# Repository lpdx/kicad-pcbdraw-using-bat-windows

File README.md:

# Running PcbDraw using bat file
Simple batch script to run [PcbDraw](https://github.com/yaqwsx/PcbDraw) on Windows environment to draw KiCAD pcbs.
The example creates plot for both sides of the pcb.

For more information about PcbDraw please check the [oficial repository](https://github.com/yaqwsx/PcbDraw).

## Dependencies

With KiCAD terminal activated, `kicad-cmd`, install the PcbDraw package using:

```pyhton
pip install pcbdraw
```

## Using it

- Update the [`make-plot-board.bat`](./make-plot-board.bat) file with the appropriate configs (line 11-16)
```cmd
REM config variables
SET ROOT_FILENAME=pwm-interface-board
SET FILE_PATH=./example/
SET CONFIG=--drill-holes --style jlcpcb-green-hasl
REM could be .svg, .png or .jpeg
SET OUTPUT_EXTENSION=.png
```

- Just give a double click on `make-plot-board.bat` or run it from terminal.

_Tested with KiCAD v6.0.10._

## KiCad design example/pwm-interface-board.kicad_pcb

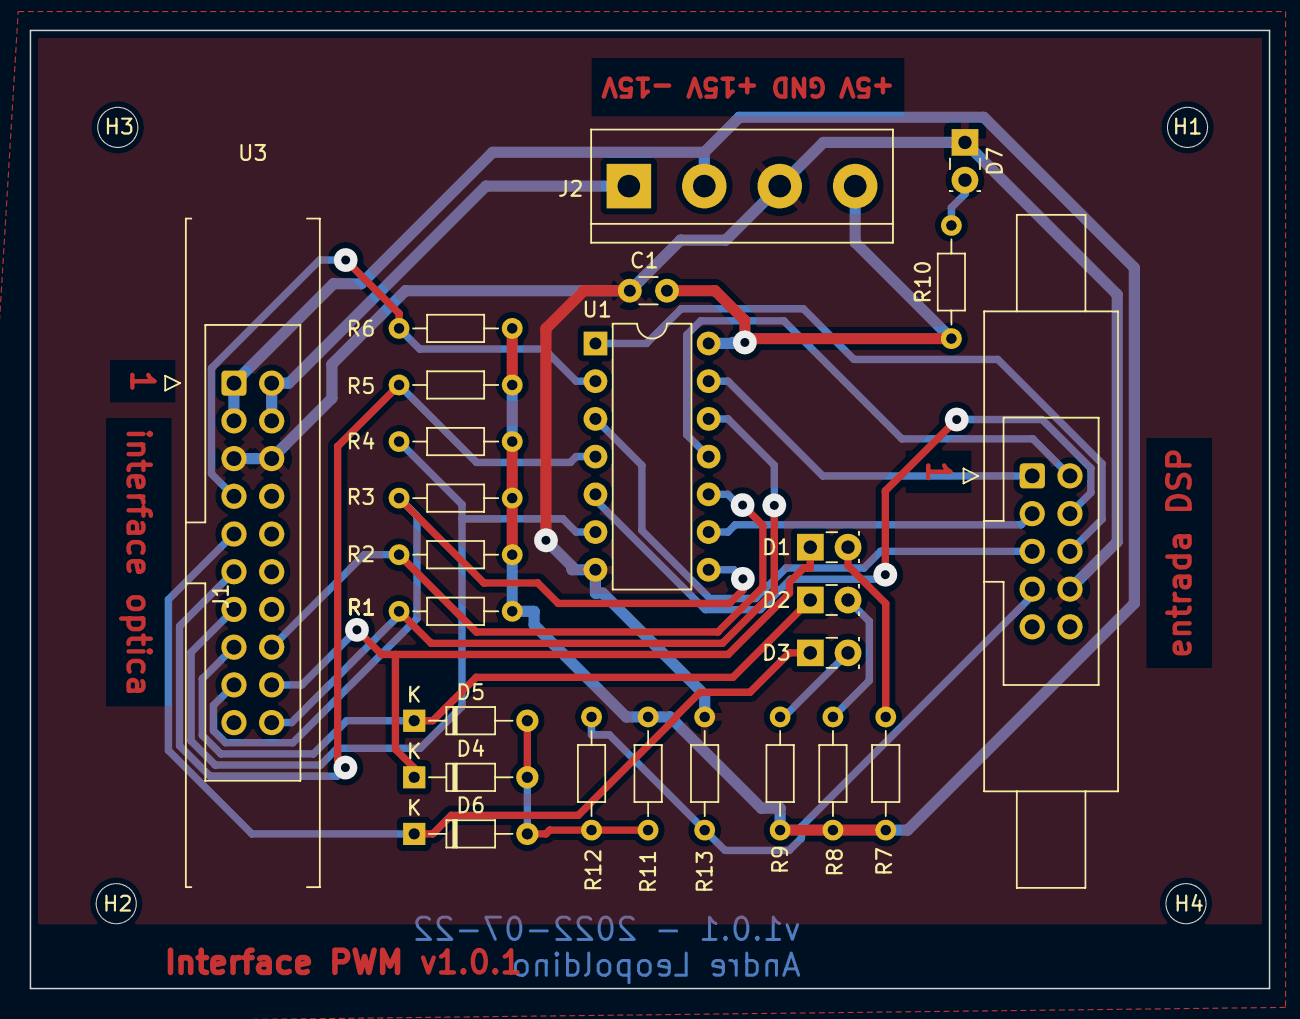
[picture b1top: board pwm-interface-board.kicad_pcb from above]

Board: 2 copper layers, 83.4 x 64.5 mm, 29 parts (0 on the bottom side), 25 nets.

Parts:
C1: 1n; C_Disc_D3.0mm_W1.6mm_P2.50mm
D1: LED YELLOW; LED_Rectangular_W3.9mm_H1.9mm
D2, D7: LED GREEN; LED_Rectangular_W3.9mm_H1.9mm
D3: LED RED; LED_Rectangular_W3.9mm_H1.9mm
D4, D5, D6: D; D_DO-34_SOD68_P7.62mm_Horizontal
H1, H2, H3, H4: MountingHole; MountingHole_2.7mm
J1: Conn_02x05_Odd_Even; IDC-Header_2x05_P2.54mm_Latch6.5mm_Vertical
J2: Screw_Terminal_01x04; TerminalBlock_bornier-4_P5.08mm
R1, R2, R3, R4, R5, R6, R7, R8, R9: 1k; R_Axial_DIN0204_L3.6mm_D1.6mm_P7.62mm_Horizontal
R10: 330; R_Axial_DIN0204_L3.6mm_D1.6mm_P7.62mm_Horizontal
R11, R13: 4k7; R_Axial_DIN0204_L3.6mm_D1.6mm_P7.62mm_Horizontal
R12: 12k; R_Axial_DIN0204_L3.6mm_D1.6mm_P7.62mm_Horizontal
U1: 74LS07; DIP-14_W7.62mm
U3: PL-117-V01; PL-117-V01-2

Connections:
+5V: C1.1, J2.4, R10.1, U1.14 (VCC)
+15V: J2.2, R1.2, R2.2, R3.2, R4.2, R5.2, R6.2, R7.2, R8.2, R9.2, R11.2, U3.1 (+15V), U3.3 (+15V)
-15V: J2.1, U3.2 (-15V), U3.4 (-15V)
/ERR_ALL: D4.2 (A), D5.2 (A), D6.2 (A), R11.1, R12.1
/LED_ERR_A: D1.2 (A), R7.1
/LED_ERR_B: D2.2 (A), R8.1
/LED_ERR_C: D3.2 (A), R9.1
DSP_ERROR\: J1.7, R12.2, R13.1
DSP_PWM_A_BOTTOM: J1.2, U1.11
DSP_PWM_A_TOP: J1.1, U1.13
DSP_PWM_B_BOTTOM: J1.4, U1.5
DSP_PWM_B_TOP: J1.3, U1.9
DSP_PWM_C_BOTTOM: J1.6, U1.1
DSP_PWM_C_TOP: J1.5, U1.3
ERROR_A\: D1.1 (K), D4.1 (K), U3.18 (A_ERR\)
ERROR_B\: D2.1 (K), D5.1 (K), U3.15 (B_ERR\)
ERROR_C\: D3.1 (K), D6.1 (K), U3.9 (C_ERR\)
GND: C1.2, D7.1 (K), J1.8, J2.3, R13.2, U1.7 (GND), U3.5 (GND), U3.6 (GND)
unnamed: D7.2 (A), R10.2
PWM_A_BOTTOM: R2.1, U1.10, U3.16 (A_BOTT)
PWM_A_TOP: R1.1, U1.12, U3.20 (A_TOP)
PWM_B_BOTTOM: R4.1, U1.6, U3.13 (B_BOTT)
PWM_B_TOP: R3.1, U1.8, U3.17 (B_TOP)
PWM_C_BOTTOM: R6.1, U1.2, U3.7 (C_BOTT)
PWM_C_TOP: R5.1, U1.4, U3.11 (C_TOP)
